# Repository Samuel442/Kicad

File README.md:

# Placas eletrônicas

## Usando software Kicad

Este repositório visa armazenar projetos eletrônicos

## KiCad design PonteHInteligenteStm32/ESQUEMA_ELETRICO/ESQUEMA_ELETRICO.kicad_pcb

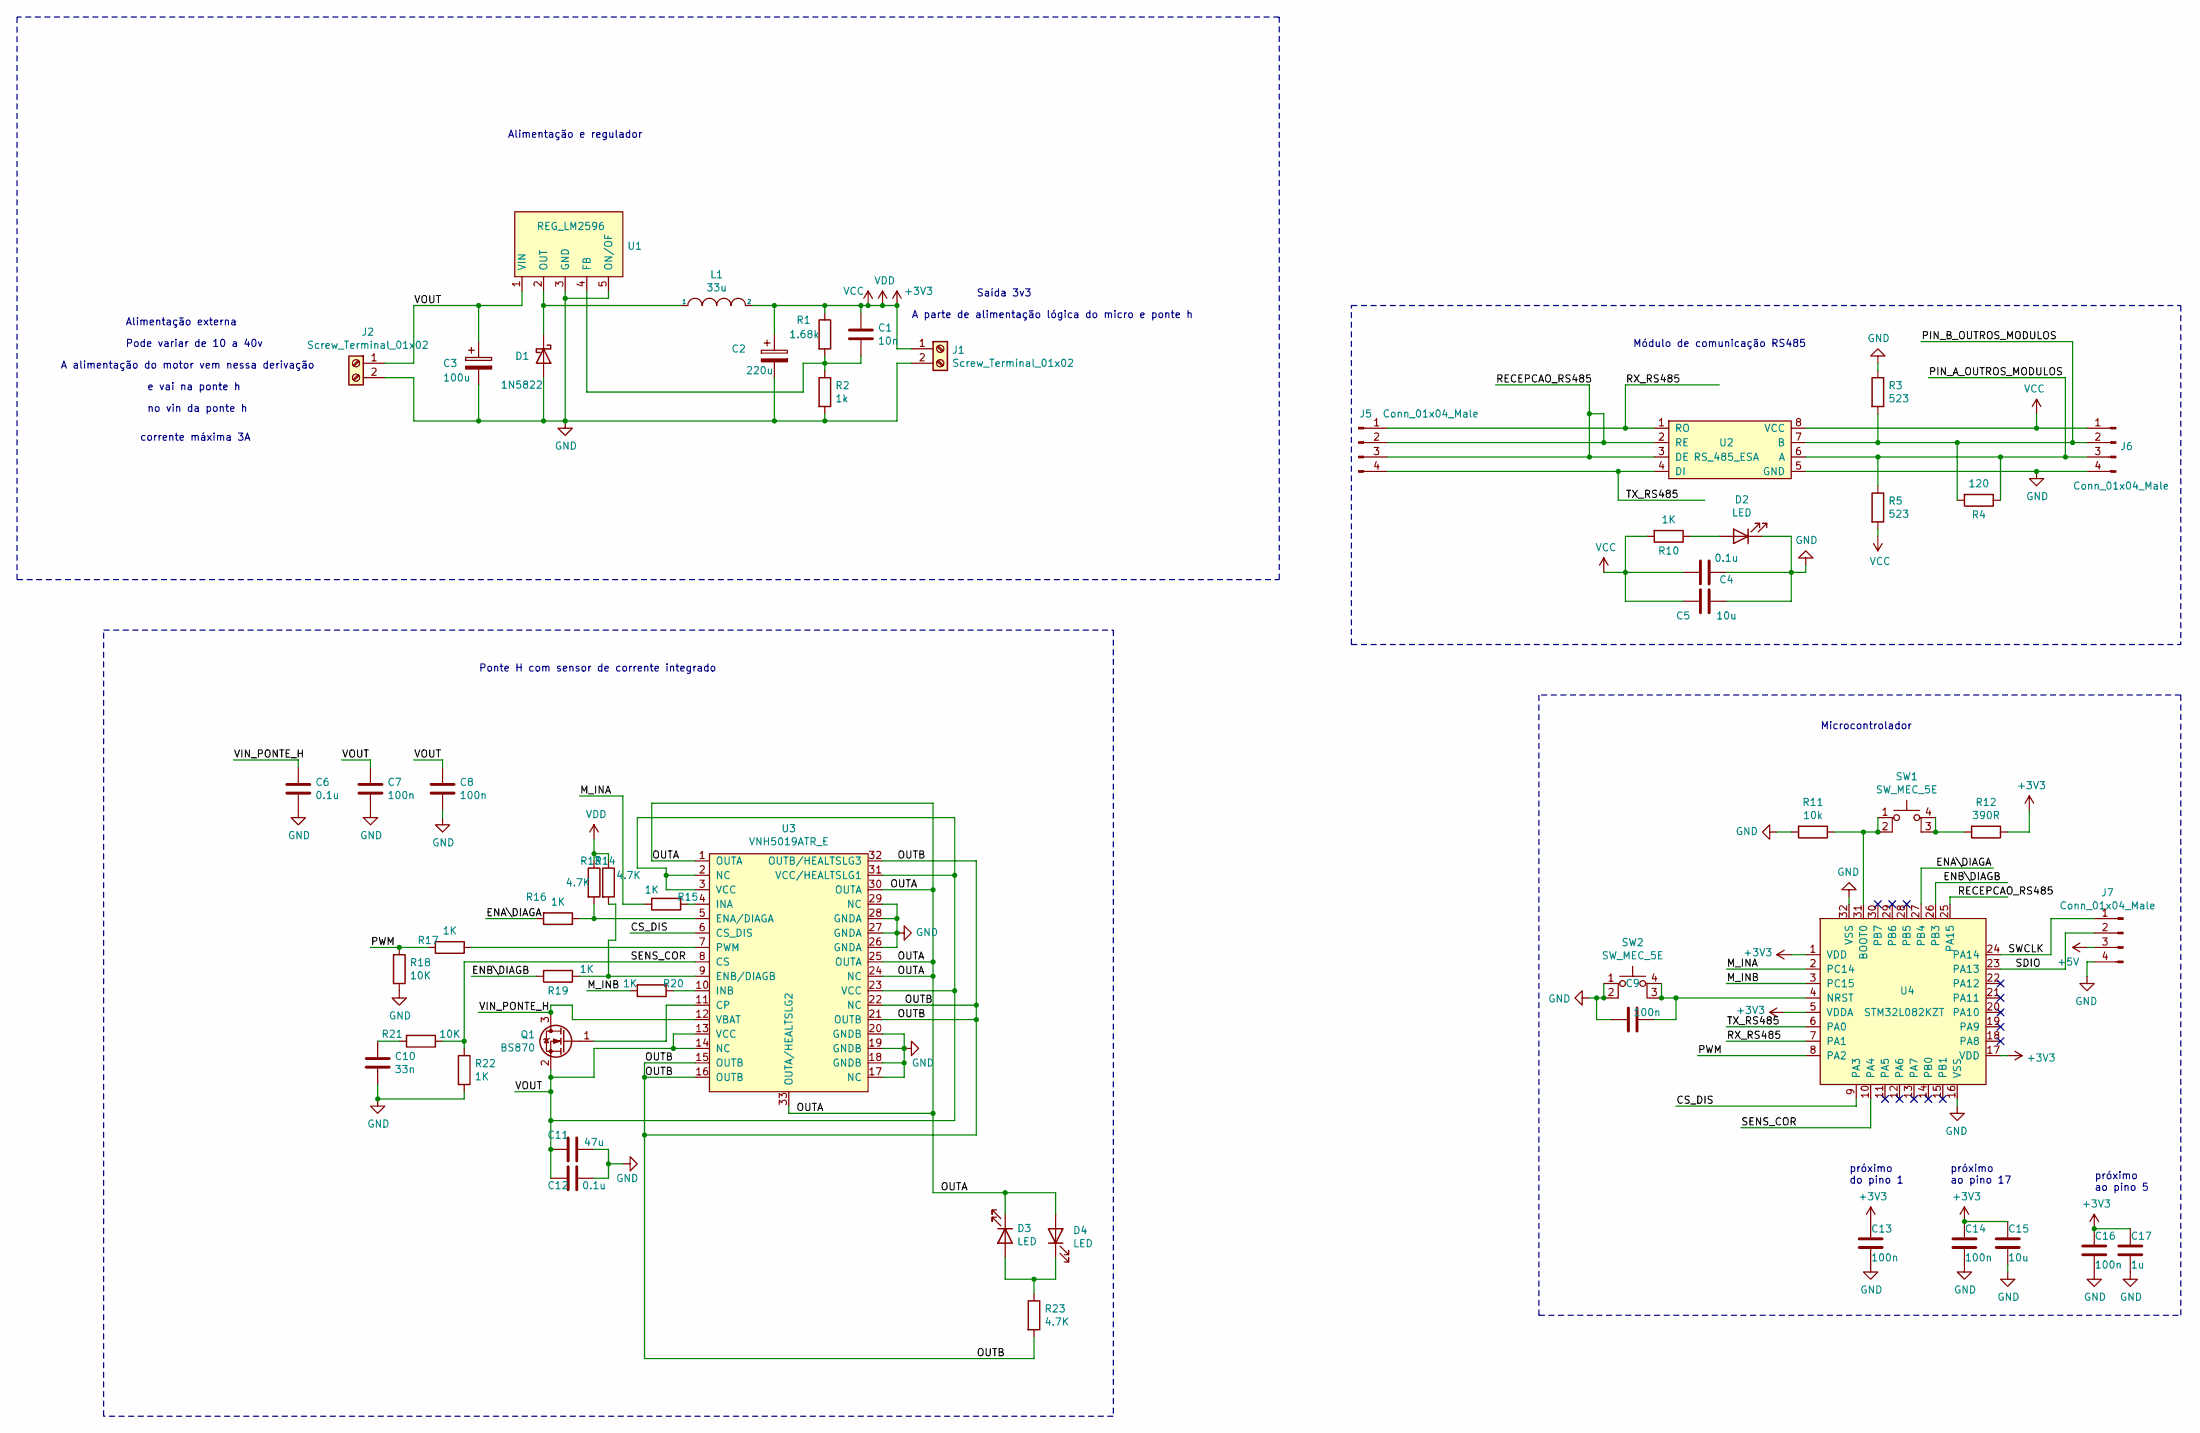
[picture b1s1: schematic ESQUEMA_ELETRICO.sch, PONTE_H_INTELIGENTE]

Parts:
C1: 10n; C_0805_2012Metric_Pad1.18x1.45mm_HandSolder
C2: 220u; CP_Elec_8x10
C3: 100u; CP_Elec_8x10
C4, C6, C12: 0.1u; C_0805_2012Metric_Pad1.18x1.45mm_HandSolder
C5, C15: 10u; C_1206_3216Metric_Pad1.33x1.80mm_HandSolder
C7, C8, C9, C13, C14, C16: 100n; C_0805_2012Metric_Pad1.18x1.45mm_HandSolder
C10: 33n; C_0805_2012Metric_Pad1.18x1.45mm_HandSolder
C11: 47u; C_1206_3216Metric_Pad1.33x1.80mm_HandSolder
C17: 1u; C_0805_2012Metric_Pad1.18x1.45mm_HandSolder
D1: 1N5822; D_3220_8050Metric_Pad2.65x5.15mm_HandSolder
D2, D3, D4: LED; LED_0805_2012Metric_Pad1.15x1.40mm_HandSolder
J1, J2: Screw_Terminal_01x02; TerminalBlock_Altech_AK300-2_P5.00mm
J5, J6, J7: Conn_01x04_Male; PinHeader_1x04_P2.54mm_Vertical
L1: 33u; L_2816_7142Metric_Pad3.20x4.45mm_HandSolder
Q1: BS870; TO-252-2
R1: 1.68k; R_0805_2012Metric_Pad1.20x1.40mm_HandSolder
R2: 1k; R_0805_2012Metric_Pad1.20x1.40mm_HandSolder
R3, R5: 523; R_0805_2012Metric_Pad1.20x1.40mm_HandSolder
R4: 120; R_0805_2012Metric_Pad1.20x1.40mm_HandSolder
R10, R15, R16, R17, R19, R20, R22: 1K; R_0805_2012Metric_Pad1.20x1.40mm_HandSolder
R11: 10k; R_0805_2012Metric_Pad1.20x1.40mm_HandSolder
R12: 390R; R_0805_2012Metric_Pad1.20x1.40mm_HandSolder
R13, R14, R23: 4.7K; R_0805_2012Metric_Pad1.20x1.40mm_HandSolder
R18, R21: 10K; R_0805_2012Metric_Pad1.20x1.40mm_HandSolder
SW1, SW2: SW_MEC_5E; SW_SPST_Omron_B3FS-101xP
U1: REG_LM2596; TO-220-5_Vertical
U2: RS_485_ESA; SOIC-8
U3: VNH5019ATR_E; IC_VNH5019ATR-E
U4: STM32L082KZT; QFP-32_10x10_Pitch0.8mm

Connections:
+3V3: C1.1, C2.1, C4.2, C5.2, C13.1, C14.1, C15.1, C16.1, C17.1, J1.1, J6.1, L1.2, R1.1, R5.2, R10.2, R12.1, R13.1, R14.1, U2.8 (VCC), U4.1 (VDD), U4.5 (VDDA), U4.17 (VDD)
+5V: J7.3
/CS_DIS: U3.6 (CS_DIS), U4.9 (PA3)
/ENA\DIAGA: R16.2, U4.27 (PB4)
/ENB\DIAGB: R19.2, U4.26 (PB3)
/M_INA: R15.2, U4.2 (PC14)
/M_INB: R20.2, U4.3 (PC15)
/OUTA: D3.1 (K), D4.2 (A), U3.1 (OUTA), U3.24 (NC), U3.25 (OUTA), U3.30 (OUTA), U3.33 (OUTA/HEALTSLG2)
/OUTB: R23.2, U3.15 (OUTB), U3.16 (OUTB), U3.21 (OUTB), U3.22 (NC), U3.32 (OUTB/HEALTSLG3)
/PIN_A_OUTROS_MODULOS: J6.3, R4.1, R5.1, U2.6 (A)
/PIN_B_OUTROS_MODULOS: J6.2, R3.2, R4.2, U2.7 (B)
/PWM: R17.2, R18.1, U4.8 (PA2)
/RECEPCAO_RS485: J5.2, J5.3, U2.2 (RE), U2.3 (DE), U4.25 (PA15)
/RX_RS485: J5.1, U2.1 (RO), U4.7 (PA1)
/SDIO: J7.2, U4.23 (PA13)
/SENS_COR: R21.1, R22.1, U3.8 (CS), U4.10 (PA4)
/SWCLK: J7.1, U4.24 (PA14)
/TX_RS485: J5.4, U2.4 (DI), U4.6 (PA0)
/VIN_PONTE_H: C6.1, Q1.3 (D), U3.12 (VBAT)
/VOUT: C3.1, C7.1, C8.1, C11.2, C12.2, J2.1, Q1.2 (S), U1.1 (VIN), U3.2 (NC), U3.3 (VCC), U3.13 (VCC), U3.14 (NC), U3.23 (VCC), U3.31 (VCC/HEALTSLG1)
GND: C2.2, C3.2, C4.1, C5.1, C6.2, C7.2, C8.2, C9.2, C10.2, C11.1, C12.1, C13.2, C14.2, C15.2, C16.2, C17.2, D1.2 (A), D2.1 (K), J1.2, J2.2, J6.4, J7.4, R2.2, R3.1, R11.2, R18.2, R22.2, SW2.1, SW2.2, U1.3 (GND), U1.5 (ON/OF), U2.5 (GND), U3.17 (NC), U3.18 (GNDB), U3.19 (GNDB), U3.20 (GNDB), U3.26 (GNDA), U3.27 (GNDA), U3.28 (GNDA), U3.29 (NC), U4.16 (VSS), U4.32 (VSS)
unnamed: C1.2, R1.2, R2.1, U1.4 (FB)
unnamed: C9.1, SW2.3 (K), SW2.4 (A), U4.4 (NRST)
unnamed: C10.1, R21.2
unnamed: D1.1 (K), L1.1, U1.2 (OUT)
unnamed: D2.2 (A), R10.1
unnamed: D3.2 (A), D4.1 (K), R23.1
unnamed: Q1.1 (G), U3.11 (CP)
unnamed: R11.1, SW1.1, SW1.2, U4.31 (BOOT0)
unnamed: R12.2, SW1.3 (K), SW1.4 (A)
unnamed: R13.2, R16.1, U3.5 (ENA/DIAGA)
unnamed: R14.2, R19.1, U3.9 (ENB/DIAGB)
unnamed: R15.1, U3.4 (INA)
unnamed: R17.1, U3.7 (PWM)
unnamed: R20.1, U3.10 (INB)

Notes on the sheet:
Alimentação e regulador
Alimentação externa
Pode variar de 10 a 40v
A alimentação do motor vem nessa derivação
e vai na ponte h
no vin da ponte h
corrente máxima 3A
Módulo de comunicação RS485
Microcontrolador
Ponte H com sensor de corrente integrado
Saída 3v3
A parte de alimentação lógica do micro e ponte h
próximo do pino 1
próximo ao pino 17
próximo ao pino 5

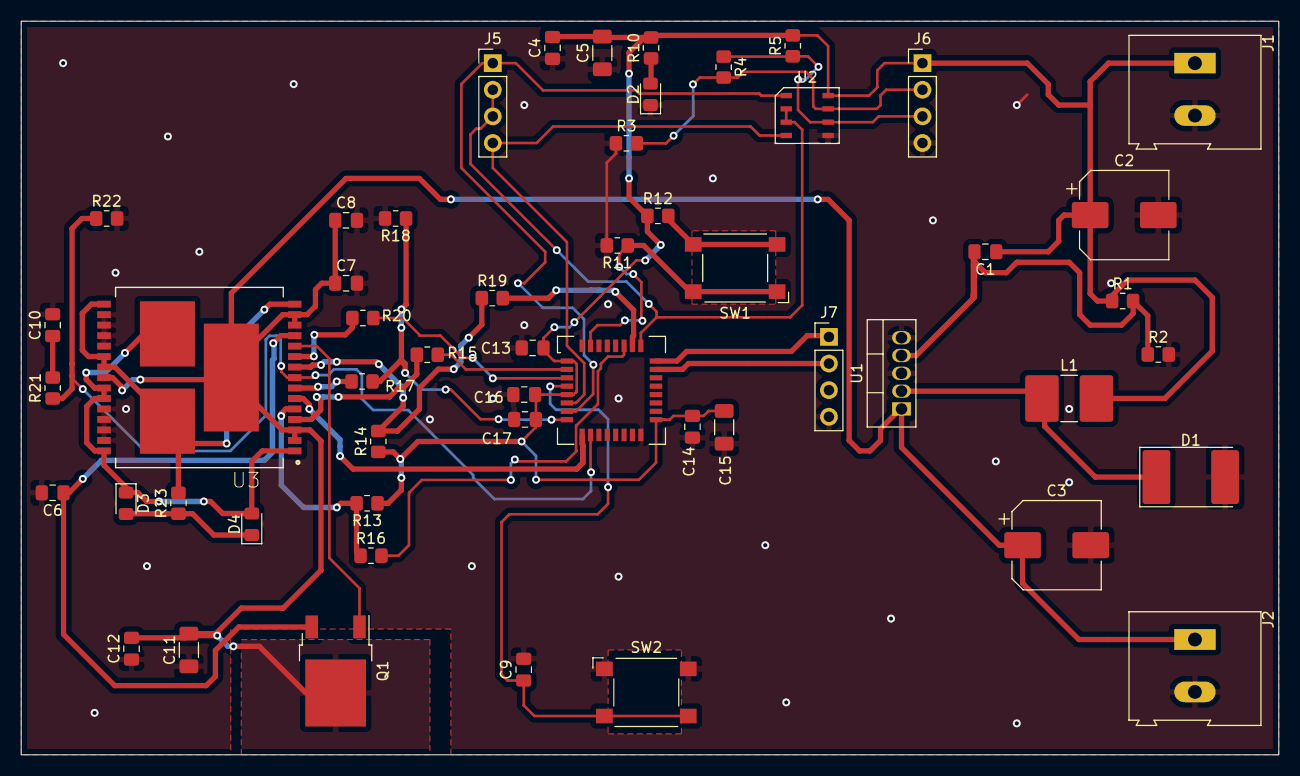
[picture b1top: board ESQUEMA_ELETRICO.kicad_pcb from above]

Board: 2 copper layers, 120.0 x 70.0 mm, 53 parts (0 on the bottom side), 34 nets.

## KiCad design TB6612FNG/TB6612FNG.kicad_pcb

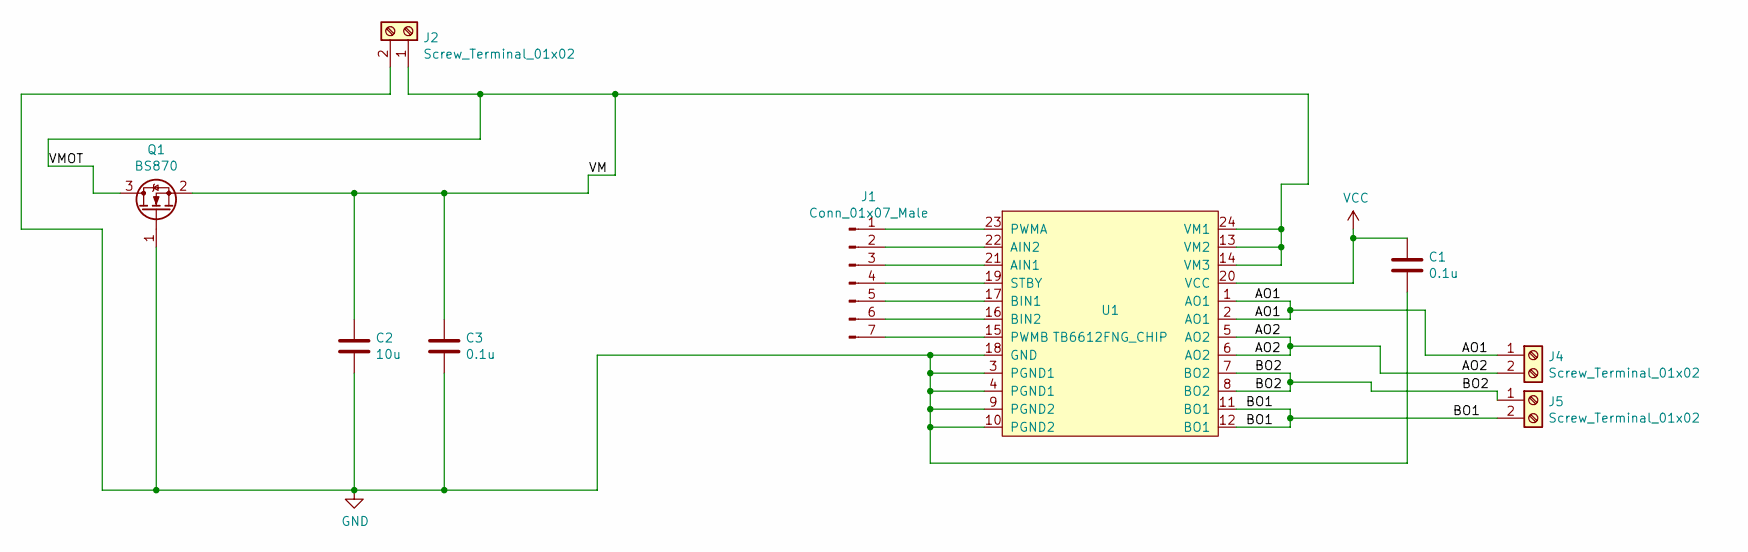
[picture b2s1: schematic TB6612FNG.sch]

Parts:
C1, C3: 0.1u; C_0805_2012Metric_Pad1.18x1.45mm_HandSolder
C2: 10u; C_1206_3216Metric_Pad1.33x1.80mm_HandSolder
J1: Conn_01x07_Male; PinHeader_1x07_P2.54mm_Vertical
J2, J4, J5: Screw_Terminal_01x02; TerminalBlock_Altech_AK300-2_P5.00mm
Q1: BS870; SOT-23
U1: TB6612FNG_CHIP; SOIC-24

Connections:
/AO1: J4.1, U1.1 (AO1), U1.2 (AO1)
/AO2: J4.2, U1.5 (AO2), U1.6 (AO2)
/BO1: J5.2, U1.11 (BO1), U1.12 (BO1)
/BO2: J5.1, U1.7 (BO2), U1.8 (BO2)
/VM: C2.1, C3.1, J2.1, Q1.2 (S), Q1.3 (D), U1.13 (VM2), U1.14 (VM3), U1.24 (VM1)
GND: C1.2, C2.2, C3.2, J2.2, Q1.1 (G), U1.3 (PGND1), U1.4 (PGND1), U1.9 (PGND2), U1.10 (PGND2), U1.18 (GND)
unnamed: J1.1, U1.23 (PWMA)
unnamed: J1.2, U1.22 (AIN2)
unnamed: J1.3, U1.21 (AIN1)
unnamed: J1.4, U1.19 (STBY)
unnamed: J1.5, U1.17 (BIN1)
unnamed: J1.6, U1.16 (BIN2)
unnamed: J1.7, U1.15 (PWMB)
VCC: C1.1, U1.20 (VCC)

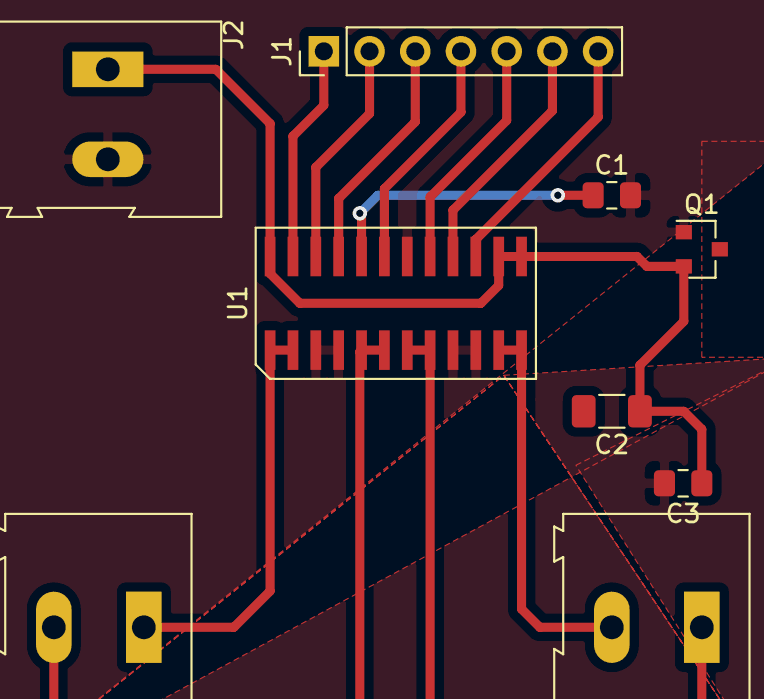
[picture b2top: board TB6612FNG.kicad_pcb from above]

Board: 2 copper layers, 9 parts (0 on the bottom side), 14 nets.

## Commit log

2023-02-11 Novos
    Projetos
2023-02-11 pont h
    inteligente
2023-02-11 criado readme
